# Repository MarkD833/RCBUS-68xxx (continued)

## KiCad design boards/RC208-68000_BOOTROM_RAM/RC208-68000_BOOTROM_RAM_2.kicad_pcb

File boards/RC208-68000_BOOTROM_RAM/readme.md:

# 1M BOOT ROM & 1M RAM board - v1.1

The old v1.0 board with the flash chips removed.

# Details
This is my RC208 BOOT ROM & RAM board and it is designed to plug into an RCBus-80 backplane with support for 1M ROM (via 2x SST39SF040 FLASH chips) and 1M RAM (via 2x Alliance Memory AS6C4008 SRAMs). The FLASH chips and SRAMs are used as a pair to allow 16-bit wide memory accesses.

This board is an enhanced version of my earlier RC107 board. This board presents the flash memory at address 0x000000 at reset and disables access to the RAM. After 4 address strobes, the flash memory is automatically moved up to address 0x700000 and the RAM becomes available at address 0x000000.

## Address Decoding
The address decoding is carried out by a 74LS138 that divides the lower 8Mb of memory space into eight 1Mb blocks.

After reset, the 74LS165 sets its Q7 output to a '1'. This '1' is then OR'd with address lines A20, A21 and A22 using 3 OR gates of the 74LS32 forcing their outputs to be a '1'. The outputs of the 3 OR gates are then fed into the A0, A1 and A2 inputs of the 74LS138 which forces output O7 of the 74LS138 low selecting the ROMs.

**68000**: After 4 address strobes, the 68000 has read the initial stack pointer and initial program counter from the ROMs and Q7 of the 74LS165 goes to a '0' allowing the outputs of the 3 OR gates to follow the logic levels on A20, A21 and A22. The 74LS138 then selects the RAM for any address between 0x000000..0x0FFFFF and the ROM for any address between 0x700000..0x7FFFFF.

**68008**: After 8 address strobes, the 68008 has read the initial stack pointer and initial program counter from the ROMs and Q7 of the 74LS165 goes to a '0' allowing the outputs of the 3 OR gates to follow the logic levels on A20, A21 and A22. The 74LS138 then selects the RAM for any address between 0x000000..0x0FFFFF and the ROM for any address between 0x700000..0x7FFFFF.

**Note:** If this board is used with an MC68302 processor, then see the note further down regarding the ability to externally remap the ROM & RAM devices.

## Bus Width 
A 74LS139 generates the read and write signals for each of the memory chips and takes care of byte or word accesses.

## DTACK
A 74LS125 is used to generate a simple /DTACK signal driven directly from the EEPROM and SRAM chip select signals without any wait period.

# Board Assembly
Assembly of the board should be fairly straightforward as there are no surface mount devices to deal with. All ICs are socketed except the 74LS32 and the 74LS165 which are soldered directly into the board.

Note, however the choice of capacitor for C9. You may find that a standard disc ceramic 100nF part is too tall and the ROM chip will not fully engage with the IC socket. On MLCC through hole capacitor should be smaller and can fit in nicely.

The only tricky bit is the cutting of one of the 32-pin DIL sockets to remove the horizontal spacers.

When fitting the 80-pin right angle connector, initially only solder a couple of pins at opposite ends of the connector so that you can make any adjustments if the board is not vertical when fitted to the backplane.

Note the ROMs must be fitted to U3 and U4 in order for the processor to boot correctly.

Finally, set JP1 and J2 for your specific configuration (see below).

# MC68302 ROM & RAM Remapping

If the version of my MC68302 monitor is used that can remap the /CS0 and /CS1 chip select signals, then U1 (74LS125), U5 (74LS138), U8 (74LS165) and U9 (74LS32) are not required but can be fitted if the board is also going to be used with a 68000 or 68010 processor later.

**WARNING** When using a 68302 processor you must set J2 so that both ROM & RAM jumpers are set to EXT so that the chip selects are controlled by the 68302. Leaving them in the LS138 position will most likely result in the processor entering the HALT state.

# Jumpers
+ J1 - Chip Selects
  + On board chip selects: jumper ROM-LS138 & RAM-LS138
  + External Chip Selects: jumper ROM-EXT & RAM-EXT
+ JP1 - /AS counter
  + 68000/68010: Solder pads 2-3
  + 68008: Solder pads 1-2

# Errors
None so far.

# History
+ v1.1 - rear silkscreen correction for JP1
+ v1.0 - initial design

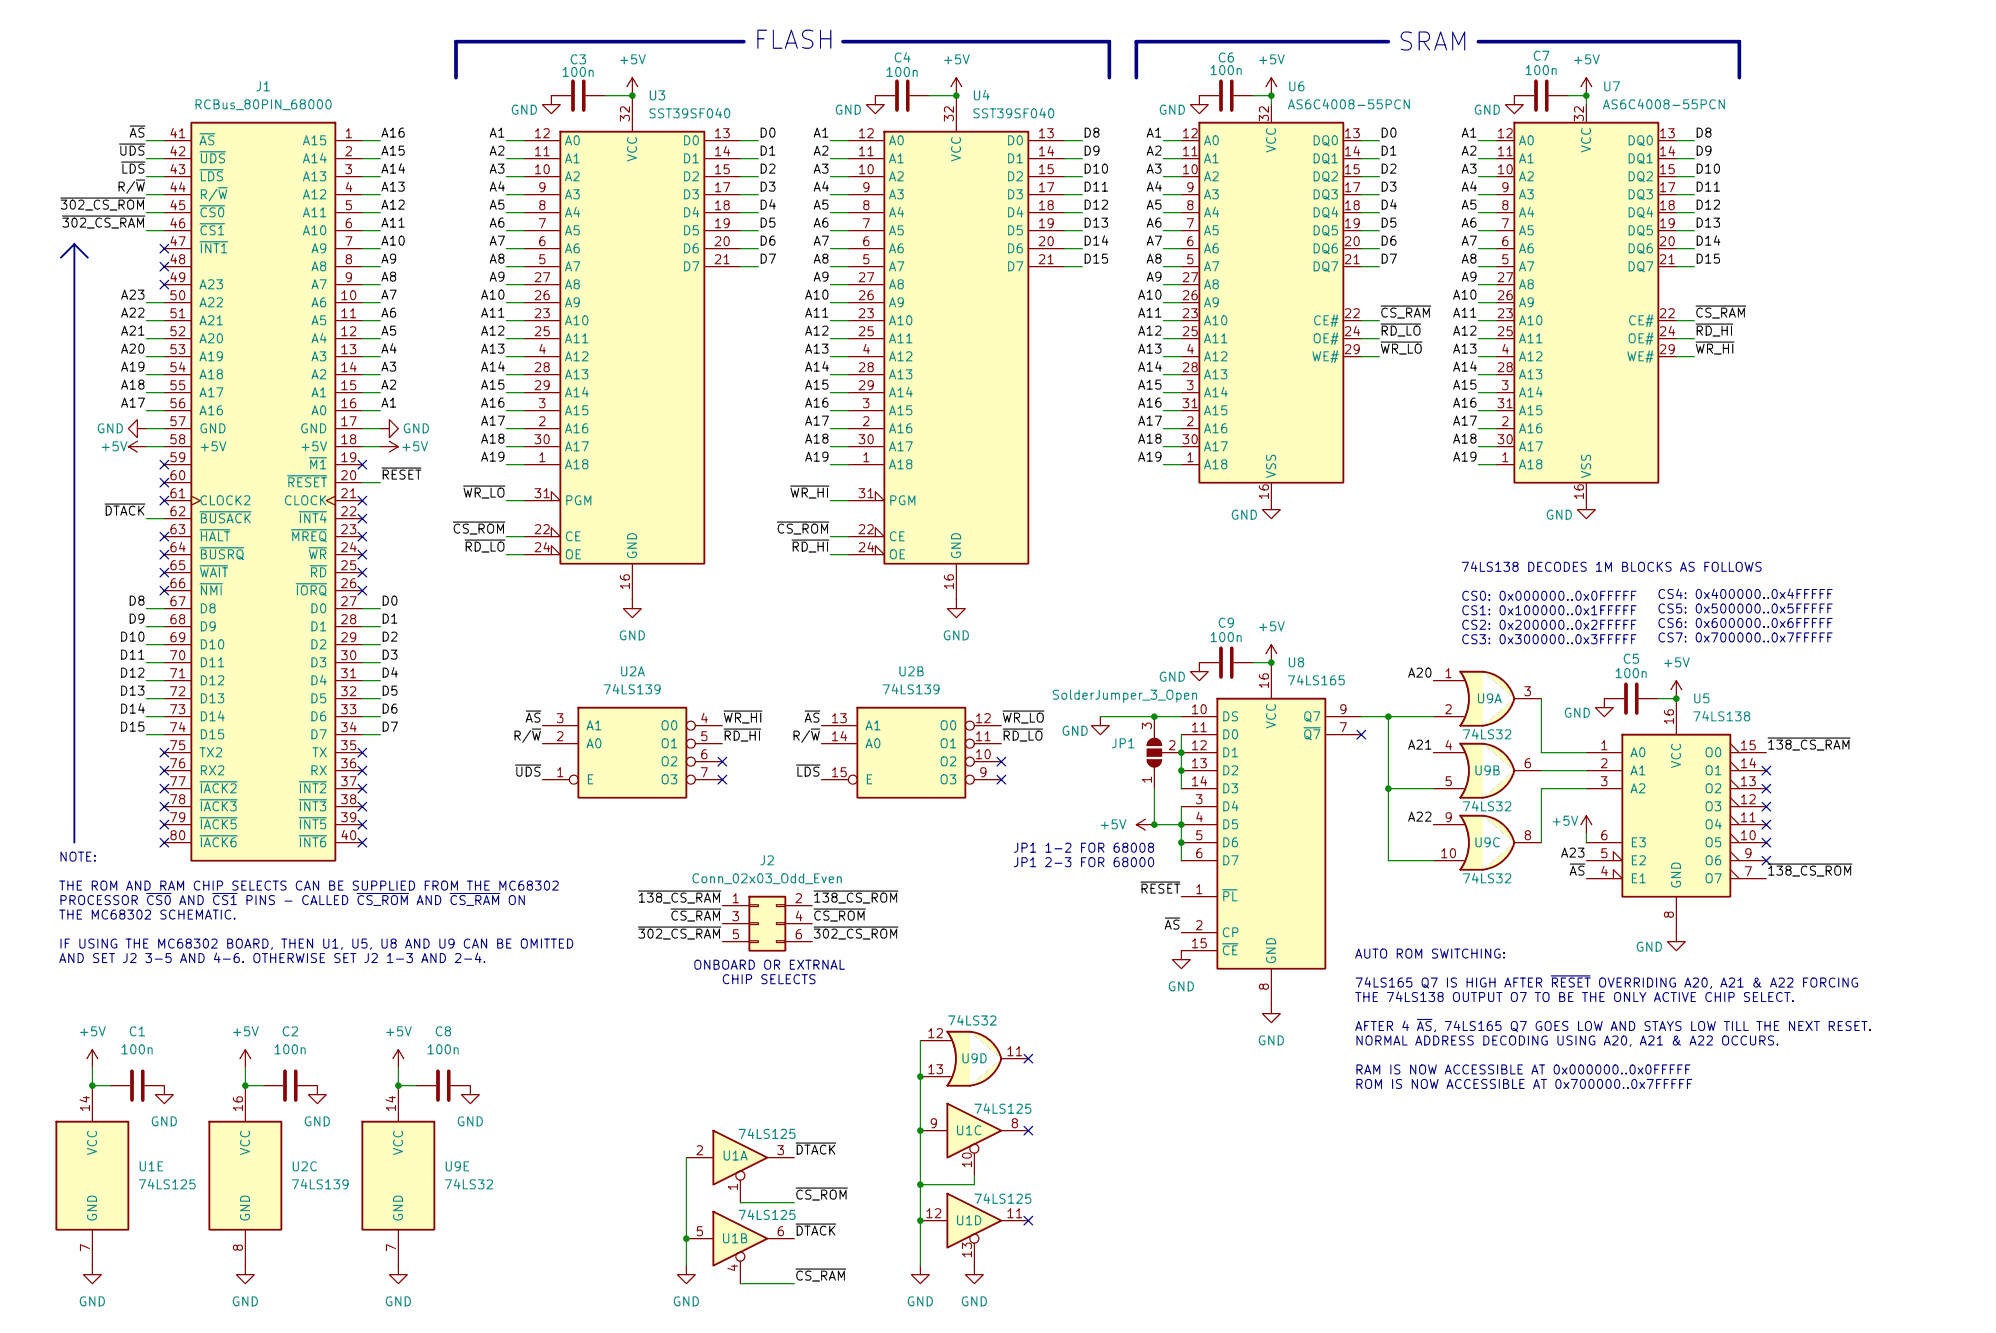
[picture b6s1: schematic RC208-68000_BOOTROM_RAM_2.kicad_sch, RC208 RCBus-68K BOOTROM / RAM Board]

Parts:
C1, C2, C3, C4, C5, C6, C7, C8, C9: 100n; C_Disc_D5.0mm_W2.5mm_P2.50mm
J1: RCBus_80PIN_68000; RCBus_80p_Medium
J2: Conn_02x03_Odd_Even; PinHeader_2x03_P2.54mm_Vertical
JP1: SolderJumper_3_Open; SolderJumper-3_P1.3mm_Open_Pad1.0x1.5mm
U1: 74LS125; DIP-14_W7.62mm
U2: 74LS139; DIP-16_W7.62mm
U3, U4: SST39SF040; DIP-32_W15.24mm
U5: 74LS138; DIP-16_W7.62mm
U6, U7: AS6C4008-55PCN; DIP-32_W15.24mm
U8: 74LS165; DIP-16_W7.62mm
U9: 74LS32; DIP-14_W7.62mm

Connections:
+5V: C1.1, C2.1, C3.2, C4.2, C5.2, C6.2, C7.2, C8.1, C9.2, J1.18 (+5V), J1.58 (+5V), JP1.1 (A), U1.14 (VCC), U2.16 (VCC), U3.32 (VCC), U4.32 (VCC), U5.6 (E3), U5.16 (VCC), U6.32 (VCC), U7.32 (VCC), U8.3 (D4), U8.4 (D5), U8.5 (D6), U8.6 (D7), U8.16 (VCC), U9.14 (VCC)
/A1: J1.16 (A0), U3.12 (A0), U4.12 (A0), U6.12 (A0), U7.12 (A0)
/A2: J1.15 (A1), U3.11 (A1), U4.11 (A1), U6.11 (A1), U7.11 (A1)
/A3: J1.14 (A2), U3.10 (A2), U4.10 (A2), U6.10 (A2), U7.10 (A2)
/A4: J1.13 (A3), U3.9 (A3), U4.9 (A3), U6.9 (A3), U7.9 (A3)
/A5: J1.12 (A4), U3.8 (A4), U4.8 (A4), U6.8 (A4), U7.8 (A4)
/A6: J1.11 (A5), U3.7 (A5), U4.7 (A5), U6.7 (A5), U7.7 (A5)
/A7: J1.10 (A6), U3.6 (A6), U4.6 (A6), U6.6 (A6), U7.6 (A6)
/A8: J1.9 (A7), U3.5 (A7), U4.5 (A7), U6.5 (A7), U7.5 (A7)
/A9: J1.8 (A8), U3.27 (A8), U4.27 (A8), U6.27 (A8), U7.27 (A8)
/A10: J1.7 (A9), U3.26 (A9), U4.26 (A9), U6.26 (A9), U7.26 (A9)
/A11: J1.6 (A10), U3.23 (A10), U4.23 (A10), U6.23 (A10), U7.23 (A10)
/A12: J1.5 (A11), U3.25 (A11), U4.25 (A11), U6.25 (A11), U7.25 (A11)
/A13: J1.4 (A12), U3.4 (A12), U4.4 (A12), U6.4 (A12), U7.4 (A12)
/A14: J1.3 (A13), U3.28 (A13), U4.28 (A13), U6.28 (A13), U7.28 (A13)
/A15: J1.2 (A14), U3.29 (A14), U4.29 (A14), U6.3 (A14), U7.3 (A14)
/A16: J1.1 (A15), U3.3 (A15), U4.3 (A15), U6.31 (A15), U7.31 (A15)
/A17: J1.56 (A16), U3.2 (A16), U4.2 (A16), U6.2 (A16), U7.2 (A16)
/A18: J1.55 (A17), U3.30 (A17), U4.30 (A17), U6.30 (A17), U7.30 (A17)
/A19: J1.54 (A18), U3.1 (A18), U4.1 (A18), U6.1 (A18), U7.1 (A18)
/A20: J1.53 (A19), U9.1
/A21: J1.52 (A20), U9.4
/A22: J1.51 (A21), U9.9
/A23: J1.50 (A22), U5.5 (E2)
/D0: J1.27 (D0), U3.13 (D0), U6.13 (DQ0)
/D1: J1.28 (D1), U3.14 (D1), U6.14 (DQ1)
/D2: J1.29 (D2), U3.15 (D2), U6.15 (DQ2)
/D3: J1.30 (D3), U3.17 (D3), U6.17 (DQ3)
/D4: J1.31 (D4), U3.18 (D4), U6.18 (DQ4)
/D5: J1.32 (D5), U3.19 (D5), U6.19 (DQ5)
/D6: J1.33 (D6), U3.20 (D6), U6.20 (DQ6)
/D7: J1.34 (D7), U3.21 (D7), U6.21 (DQ7)
/D8: J1.67 (D8), U4.13 (D0), U7.13 (DQ0)
/D9: J1.68 (D9), U4.14 (D1), U7.14 (DQ1)
/D10: J1.69 (D10), U4.15 (D2), U7.15 (DQ2)
/D11: J1.70 (D11), U4.17 (D3), U7.17 (DQ3)
/D12: J1.71 (D12), U4.18 (D4), U7.18 (DQ4)
/D13: J1.72 (D13), U4.19 (D5), U7.19 (DQ5)
/D14: J1.73 (D14), U4.20 (D6), U7.20 (DQ6)
/D15: J1.74 (D15), U4.21 (D7), U7.21 (DQ7)
/R/~W: J1.44 (R/~W), U2.2 (A0), U2.14 (A0)
/~138_CS_RAM: J2.1, U5.15 (O0)
/~138_CS_ROM: J2.2, U5.7 (O7)
/~302_CS_RAM: J1.46 (~CS1), J2.5
/~302_CS_ROM: J1.45 (~CS0), J2.6
/~AS: J1.41 (~AS), U2.3 (A1), U2.13 (A1), U5.4 (E1), U8.2 (CP)
/~CS_RAM: J2.3, U1.4, U6.22 (CE#), U7.22 (CE#)
/~CS_ROM: J2.4, U1.1, U3.22 (CE), U4.22 (CE)
/~DTACK: J1.62 (~BUSACK), U1.3, U1.6
/~LDS: J1.43 (~LDS), U2.15 (E)
/~RD_HI: U2.5 (O1), U4.24 (OE), U7.24 (OE#)
/~RD_LO: U2.11 (O1), U3.24 (OE), U6.24 (OE#)
/~RESET: J1.20 (~RESET), U8.1 (~PL)
/~UDS: J1.42 (~UDS), U2.1 (E)
/~WR_HI: U2.4 (O0), U4.31 (PGM), U7.29 (WE#)
/~WR_LO: U2.12 (O0), U3.31 (PGM), U6.29 (WE#)
GND: C1.2, C2.2, C3.1, C4.1, C5.1, C6.1, C7.1, C8.2, C9.1, J1.17 (GND), J1.57 (GND), JP1.3 (B), U1.2, U1.5, U1.7 (GND), U1.9, U1.10, U1.12, U1.13, U2.8 (GND), U3.16 (GND), U4.16 (GND), U5.8 (GND), U6.16 (VSS), U7.16 (VSS), U8.8 (GND), U8.10 (DS), U8.15 (~CE), U9.7 (GND), U9.12, U9.13
unnamed: JP1.2 (C), U8.11 (D0), U8.12 (D1), U8.13 (D2), U8.14 (D3)
unnamed: U5.1 (A0), U9.3
unnamed: U5.2 (A1), U9.6
unnamed: U5.3 (A2), U9.8
unnamed: U8.9 (Q7), U9.2, U9.5, U9.10

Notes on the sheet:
CS4: 0x400000..0x4FFFFF CS5: 0x500000..0x5FFFFF CS6: 0x600000..0x6FFFFF CS7: 0x700000..0x7FFFFF
FLASH
NOTE: THE ROM AND RAM CHIP SELECTS CAN BE SUPPLIED FROM THE MC68302 PROCESSOR ~{CS0} AND ~{CS1} PINS - CALLED ~{CS_ROM} AND ~{CS_RAM} ON THE MC68302 SCHEMATIC. IF USING THE MC68302 BOARD, THEN U1, U5, U8 AND U9 CAN BE OMITTED AND SET J2 3-5 AND 4-6. OTHERWISE SET J2 1-3 AND 2-4.
AUTO ROM SWITCHING: 74LS165 Q7 IS HIGH AFTER ~{RESET} OVERRIDING A20, A21 & A22 FORCING THE 74LS138 OUTPUT O7 TO BE THE ONLY ACTIVE CHIP SELECT. AFTER 4 ~{AS}, 74LS165 Q7 GOES LOW AND STAYS LOW TILL THE NEXT RESET. NORMAL ADDRESS DECODING USING A20, A21 & A22 OCCURS. RAM IS NOW ACCESSIBLE AT 0x0000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
JP1 1-2 FOR 68008 JP1 2-3 FOR 68000
74LS138 DECODES 1M BLOCKS AS FOLLOWS CS0: 0x000000..0x0FFFFF CS1: 0x100000..0x1FFFFF CS2: 0x200000..0x2FFFFF CS3: 0x300000..0x3FFFFF
ONBOARD OR EXTRNAL CHIP SELECTS
SRAM

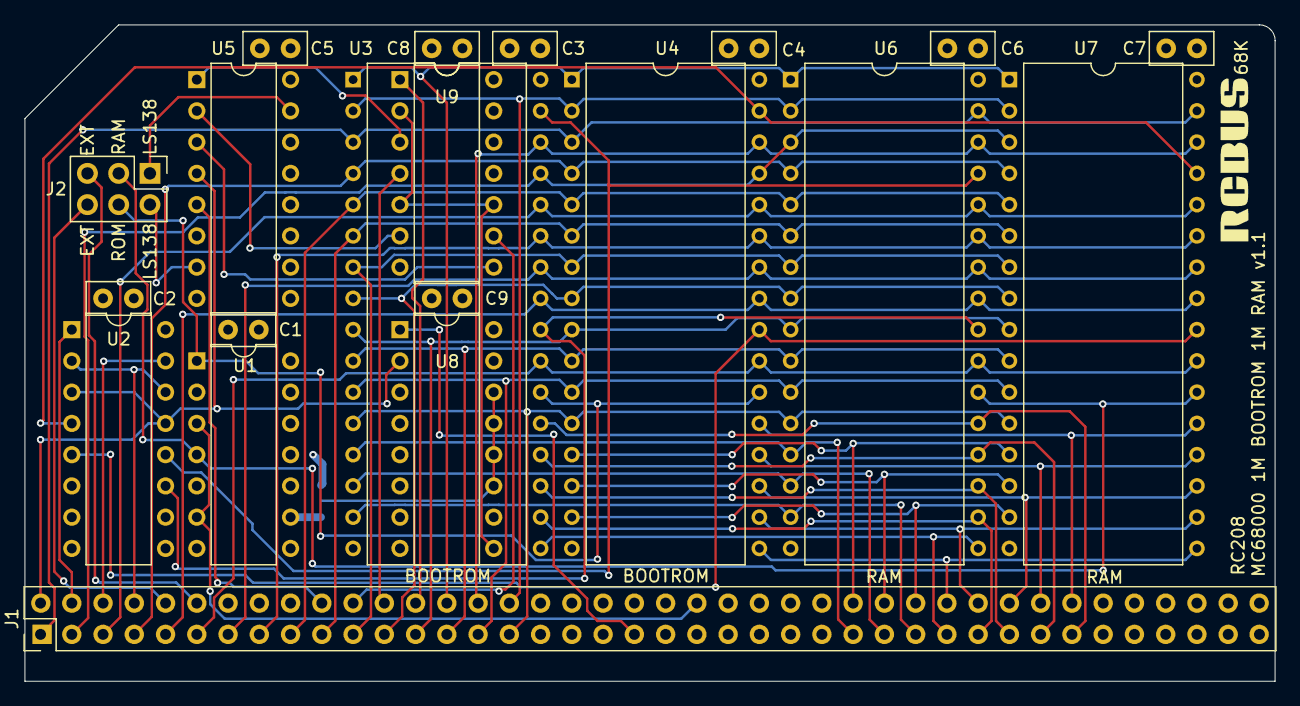
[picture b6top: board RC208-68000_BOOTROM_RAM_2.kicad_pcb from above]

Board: 4 copper layers, 101.6 x 53.3 mm, 21 parts (1 on the bottom side), 62 nets.

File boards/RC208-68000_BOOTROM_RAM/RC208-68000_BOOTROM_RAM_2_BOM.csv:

"Reference","Value","Qty","Description"
"C1,C2,C3,C4,C5,C6,C7,C8,C9","100n","9","Unpolarized ceramic capacitor"
"J1","RCBus_80PIN_68000","1","Generic connector, double row, 02x40, right angle"
"J2","Conn_02x03_Odd_Even","1","Generic connector, double row, 02x03, odd/even pin numbering scheme (row 1 odd numbers, row 2 even numbers), script generated (kicad-library-utils/schlib/autogen/connector/)"
"U1","74LS125","1","Quad buffer 3-State outputs"
"U2","74LS139","1","Dual Decoder 1 of 4, Active low outputs"
"U3,U4","SST39SF040","2","Silicon Storage Technology (SSF) 512k x 8 Flash ROM"
"U5","74LS138","1","Decoder 3 to 8 active low outputs"
"U6,U7","AS6C4008-55PCN","2","512K x 8 Low Power CMOS RAM, DIP-32"
"U8","74LS165","1","Shift Register 8-bit, parallel load"
"U9","74LS32","1","Quad 2-input OR"
